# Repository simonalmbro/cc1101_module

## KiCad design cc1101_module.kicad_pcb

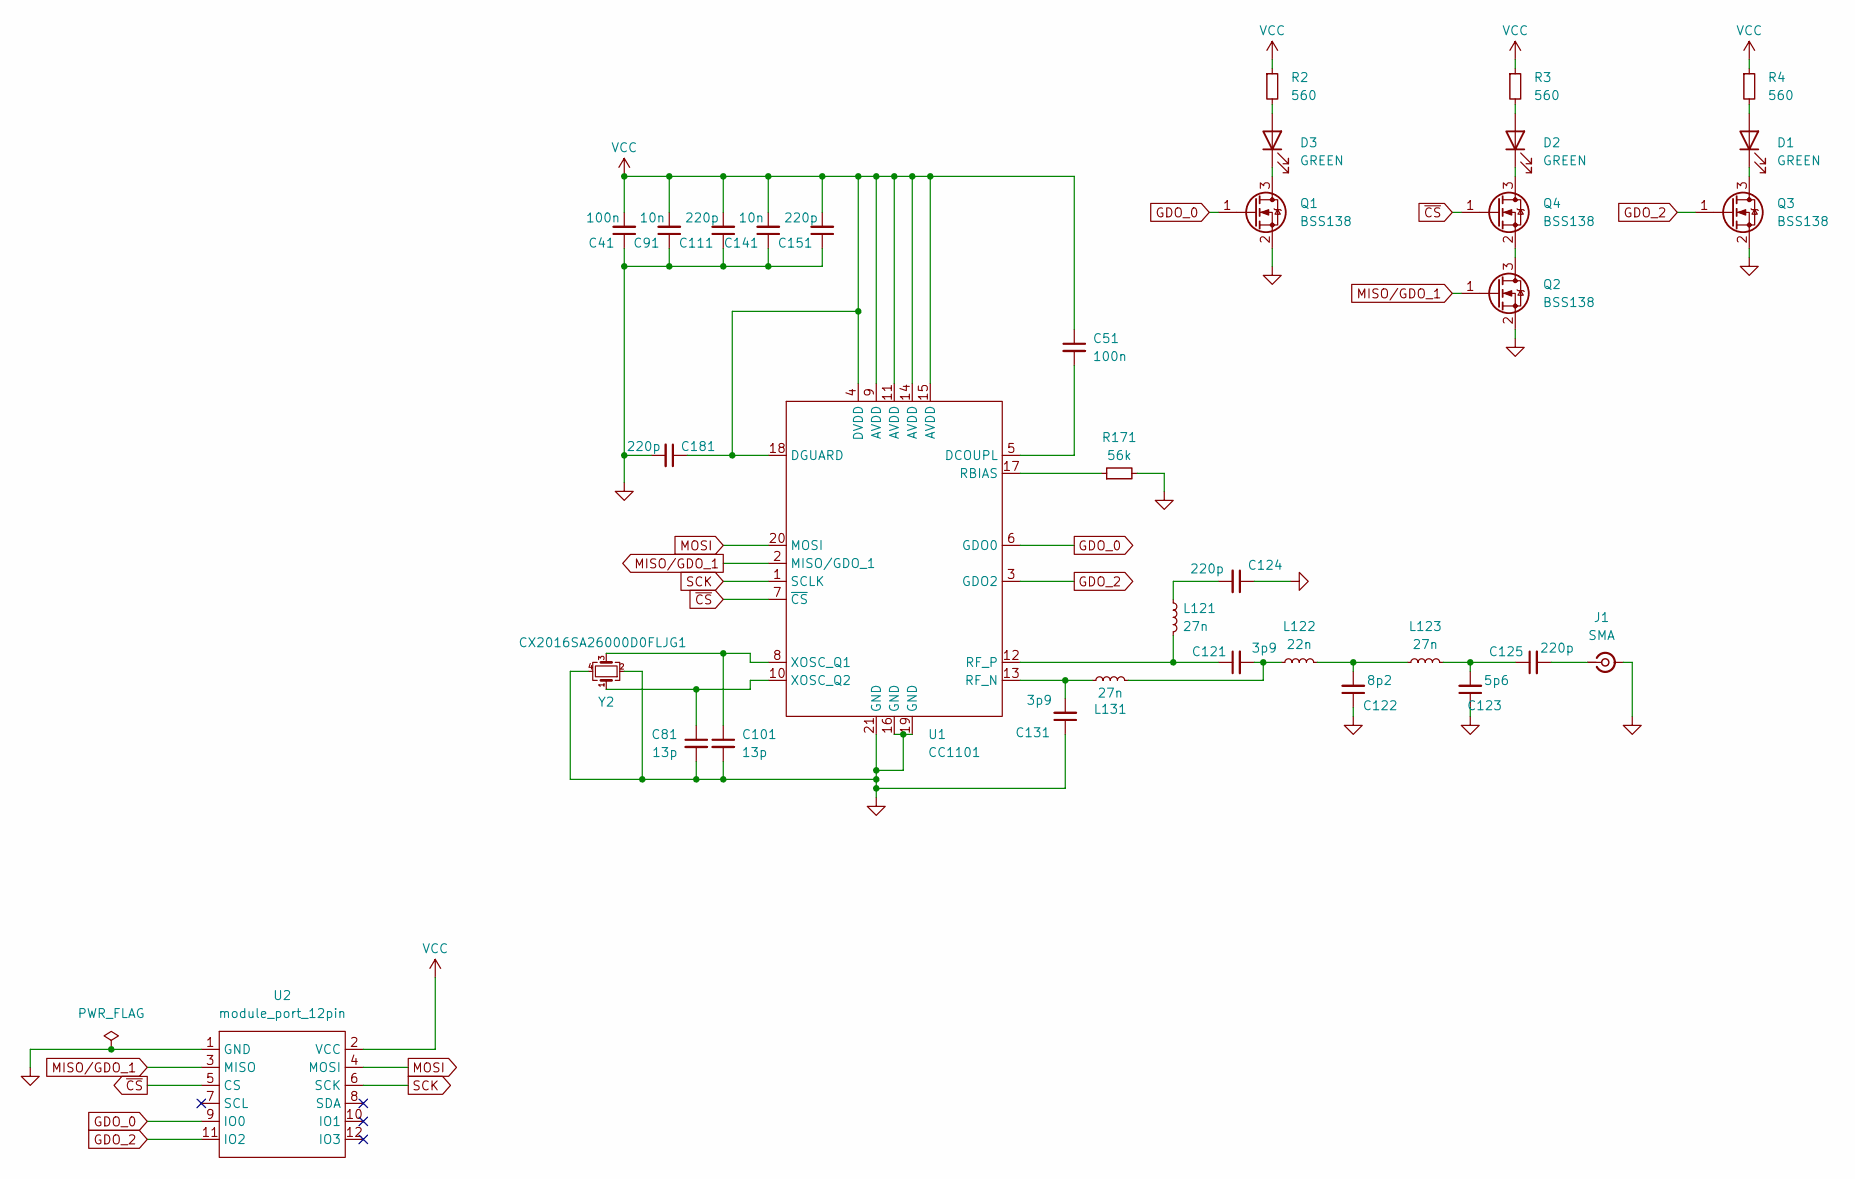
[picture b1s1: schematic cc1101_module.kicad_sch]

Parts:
C41, C51: 100n; C_0402_1005Metric
C81, C101: 13p; C_0402_1005Metric
C91, C141: 10n; C_0402_1005Metric
C111, C124, C125, C151, C181: 220p; C_0402_1005Metric
C121, C131: 3p9; C_0402_1005Metric
C122: 8p2; C_0402_1005Metric
C123: 5p6; C_0402_1005Metric
D1, D2, D3: GREEN; LED_0603_1608Metric
J1: SMA; GCT RFPC-SMA31-FN-095
L121, L123, L131: 27n; L_0402_1005Metric
L122: 22n; L_0402_1005Metric
Q1, Q2, Q3, Q4: BSS138; SOT-23
R2, R3, R4: 560; R_0603_1608Metric
R171: 56k; R_0402_1005Metric
U1: CC1101; Texas_RGP0020H_VQFN-20-1EP_4x4mm_P0.5mm_EP2.4x2.4mm_Thermal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
U2: module_port_12pin; PinHeader_2x06_P2.54mm_Horizontal
Y2: CX2016SA26000D0FLJG1

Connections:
GDO_0: Q1.1 (G), U1.6 (GDO0), U2.9 (IO0)
GDO_2: Q3.1 (G), U1.3 (GDO2), U2.11 (IO2)
GND: C41.1, C81.2, C91.1, C101.2, C111.1, C122.1, C123.1, C124.1, C131.1, C141.1, C151.1, C181.2, J1.2 (Ext), Q1.2 (S), Q2.2 (S), Q3.2 (S), R171.2, U1.16 (GND), U1.19 (GND), U1.21 (GND), U2.1 (GND), Y2.2, Y2.4
MISO/GDO_1: Q2.1 (G), U1.2 (MISO/GDO_1), U2.3 (MISO)
MOSI: U1.20 (MOSI), U2.4 (MOSI)
unnamed: C121.2, L122.1, L131.2
unnamed: C122.2, L122.2, L123.1
unnamed: C123.2, C125.1, L123.2
unnamed: C124.2, L121.1
unnamed: D1.2 (A), R4.2
unnamed: D1.1 (K), Q3.3 (D)
unnamed: D2.2 (A), R3.2
unnamed: D2.1 (K), Q4.3 (D)
unnamed: D3.2 (A), R2.2
unnamed: D3.1 (K), Q1.3 (D)
unnamed: C125.2, J1.1 (In)
unnamed: Q2.3 (D), Q4.2 (S)
unnamed: C51.2, U1.5 (DCOUPL)
unnamed: R171.1, U1.17 (RBIAS)
unnamed: C131.2, L131.1, U1.13 (RF_N)
unnamed: C121.1, L121.2, U1.12 (RF_P)
unnamed: C101.1, U1.8 (XOSC_Q1), Y2.3
unnamed: C81.1, U1.10 (XOSC_Q2), Y2.1
SCK: U1.1 (SCLK), U2.6 (SCK)
VCC: C41.2, C51.1, C91.2, C111.2, C141.2, C151.2, C181.1, R2.1, R3.1, R4.1, U1.4 (DVDD), U1.9 (AVDD), U1.11 (AVDD), U1.14 (AVDD), U1.15 (AVDD), U1.18 (DGUARD), U2.2 (VCC)
~CS: Q4.1 (G), U1.7 (~CS), U2.5 (CS)

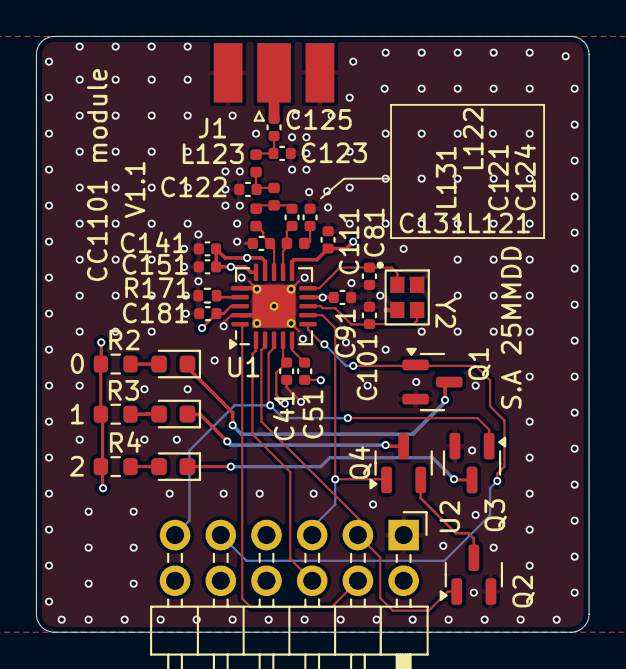
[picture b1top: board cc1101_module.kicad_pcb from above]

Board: 4 copper layers, 30.7 x 33.1 mm, 34 parts (0 on the bottom side), 26 nets.

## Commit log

2025-03-13 Version 1.0, has incorrect footprint for the crystal oscillator but works when turned 90 degrees.
2025-03-22 Updated footprint for the oscillator
